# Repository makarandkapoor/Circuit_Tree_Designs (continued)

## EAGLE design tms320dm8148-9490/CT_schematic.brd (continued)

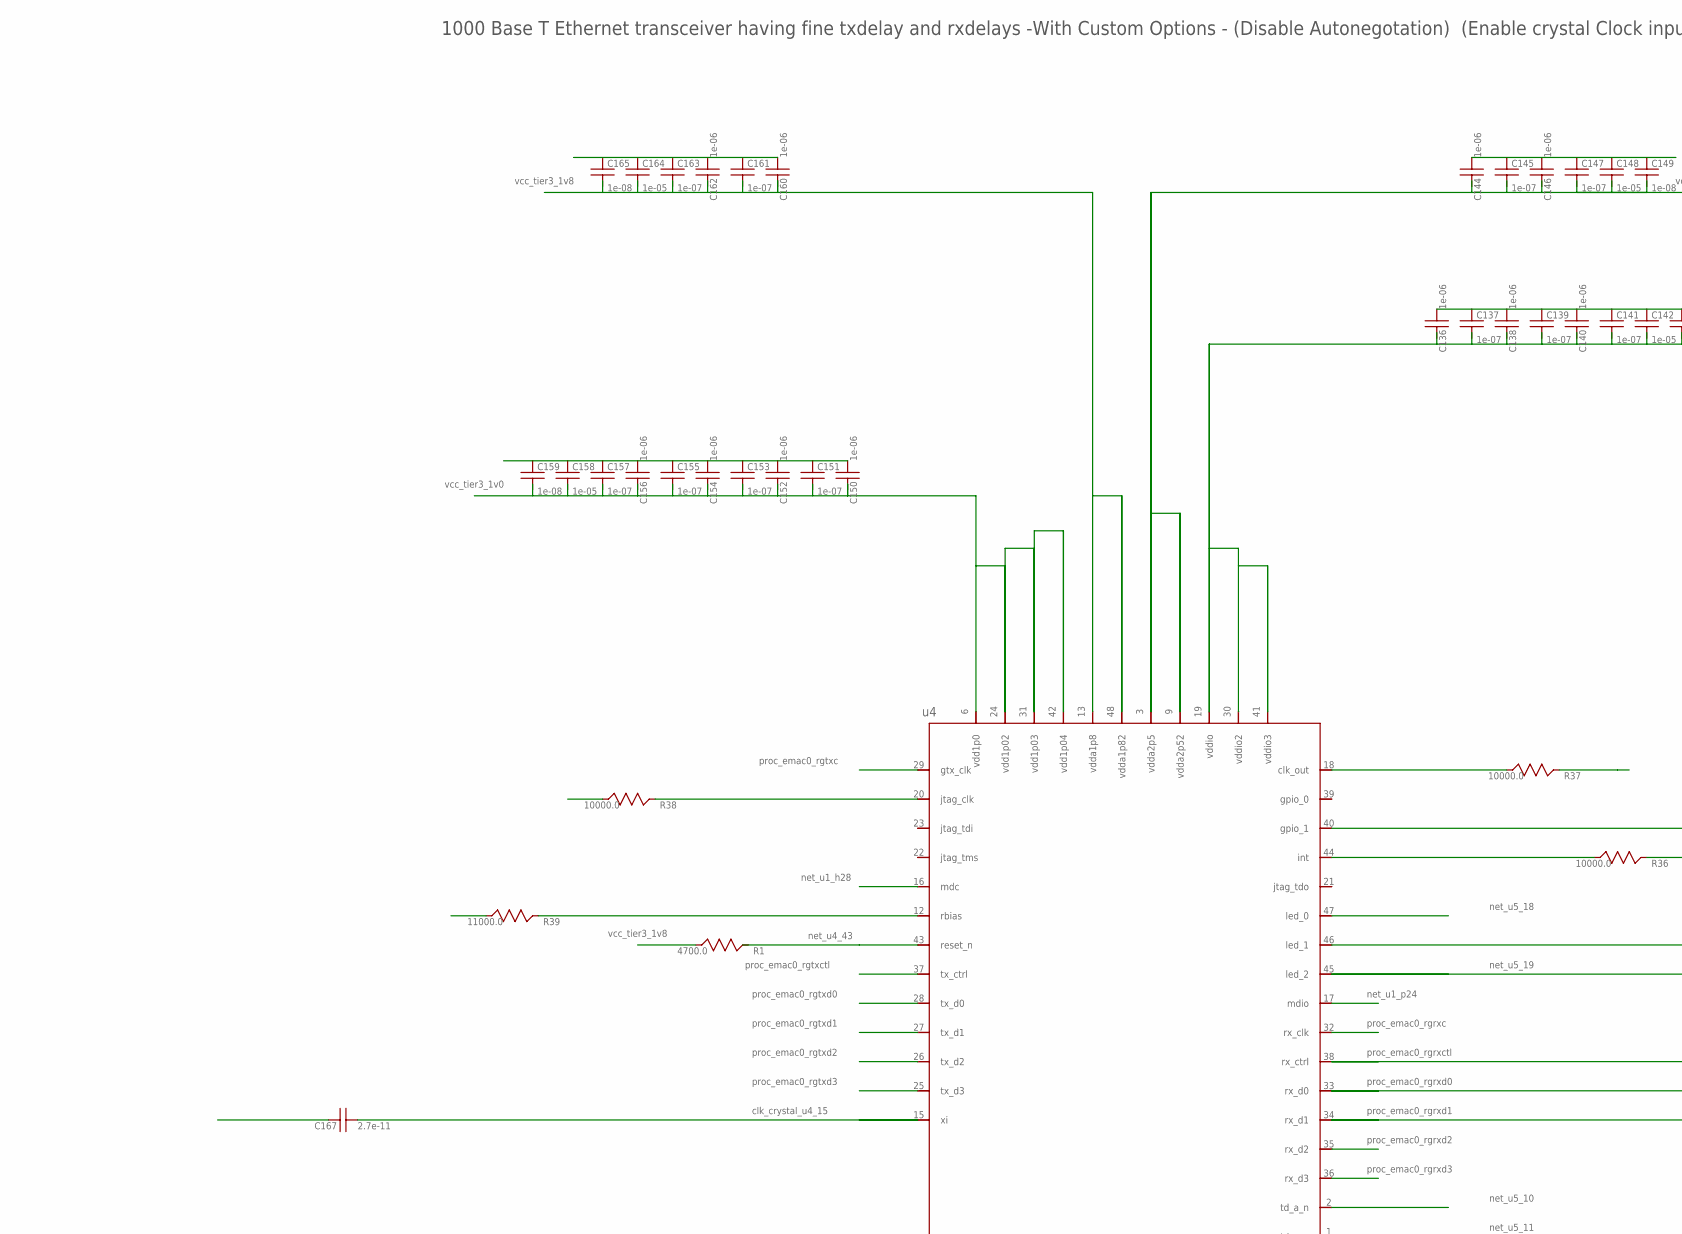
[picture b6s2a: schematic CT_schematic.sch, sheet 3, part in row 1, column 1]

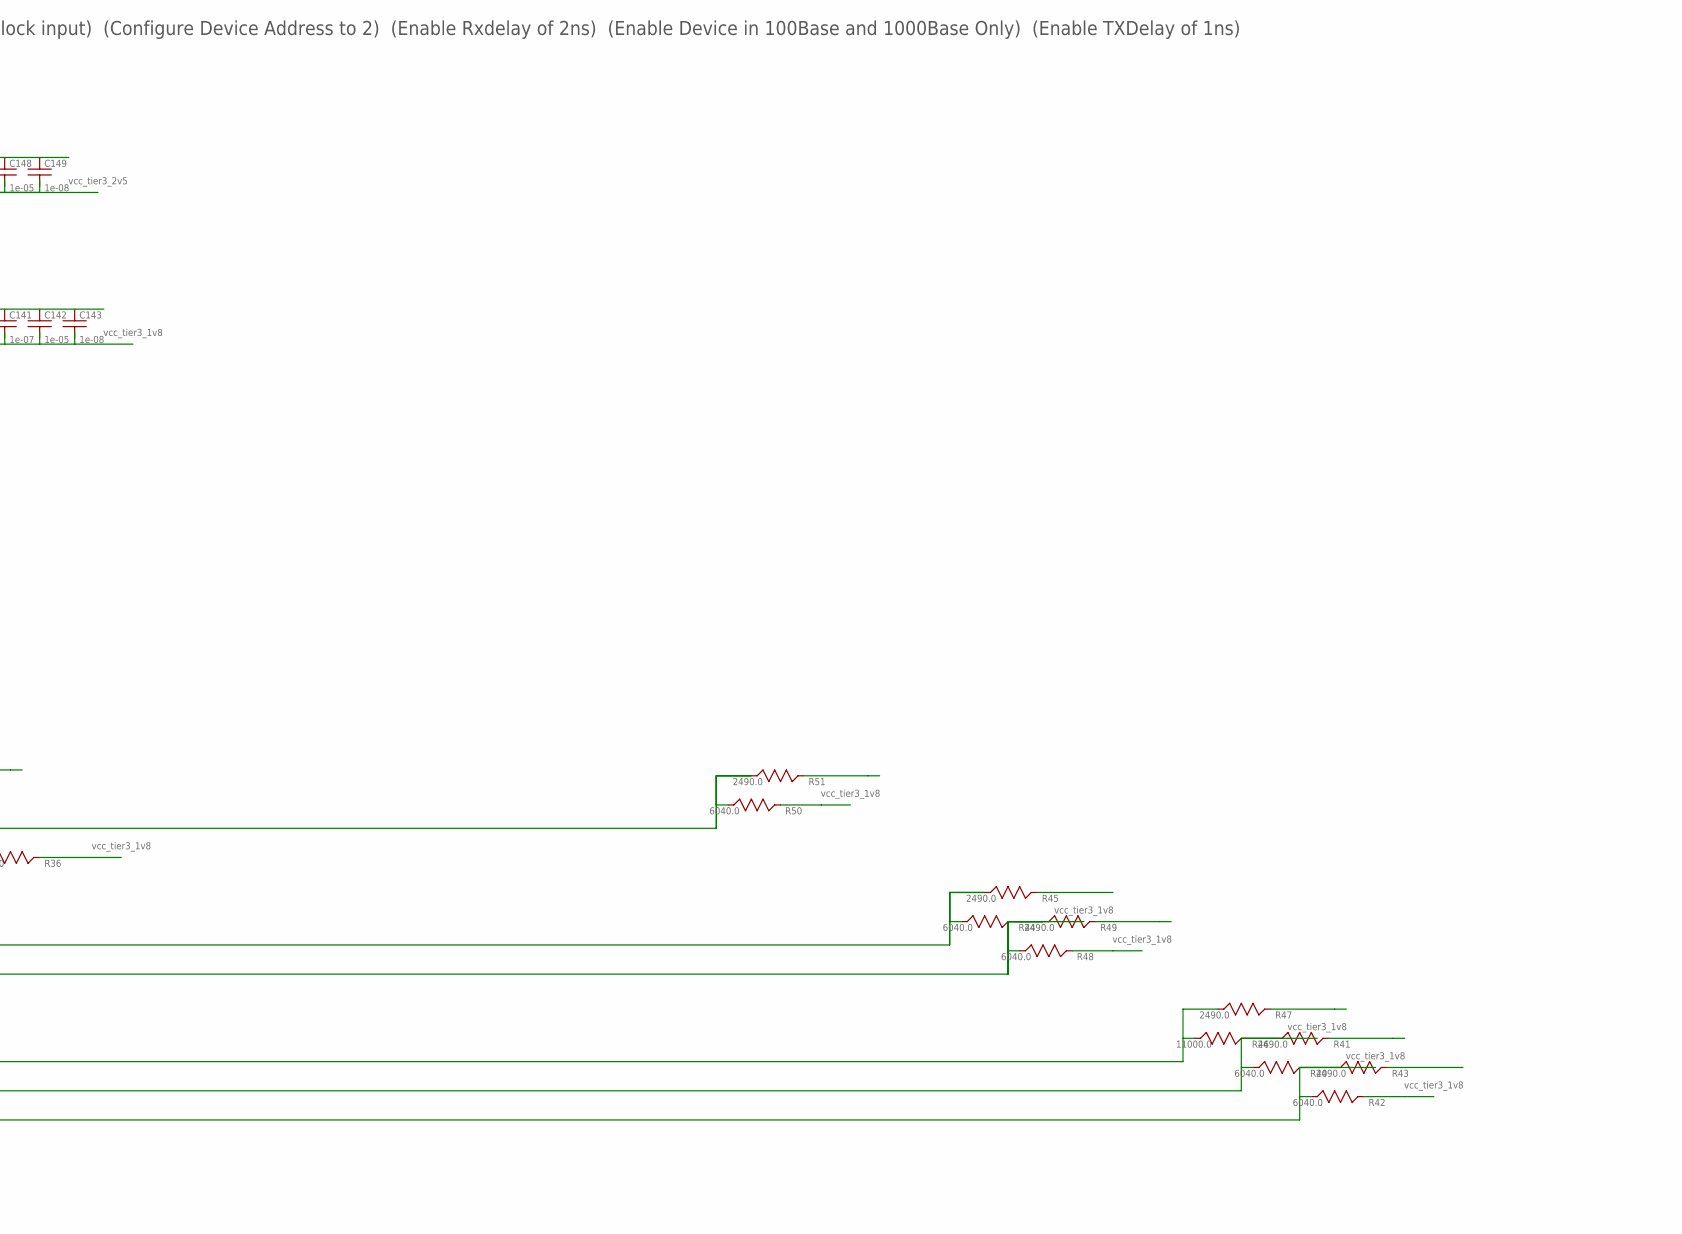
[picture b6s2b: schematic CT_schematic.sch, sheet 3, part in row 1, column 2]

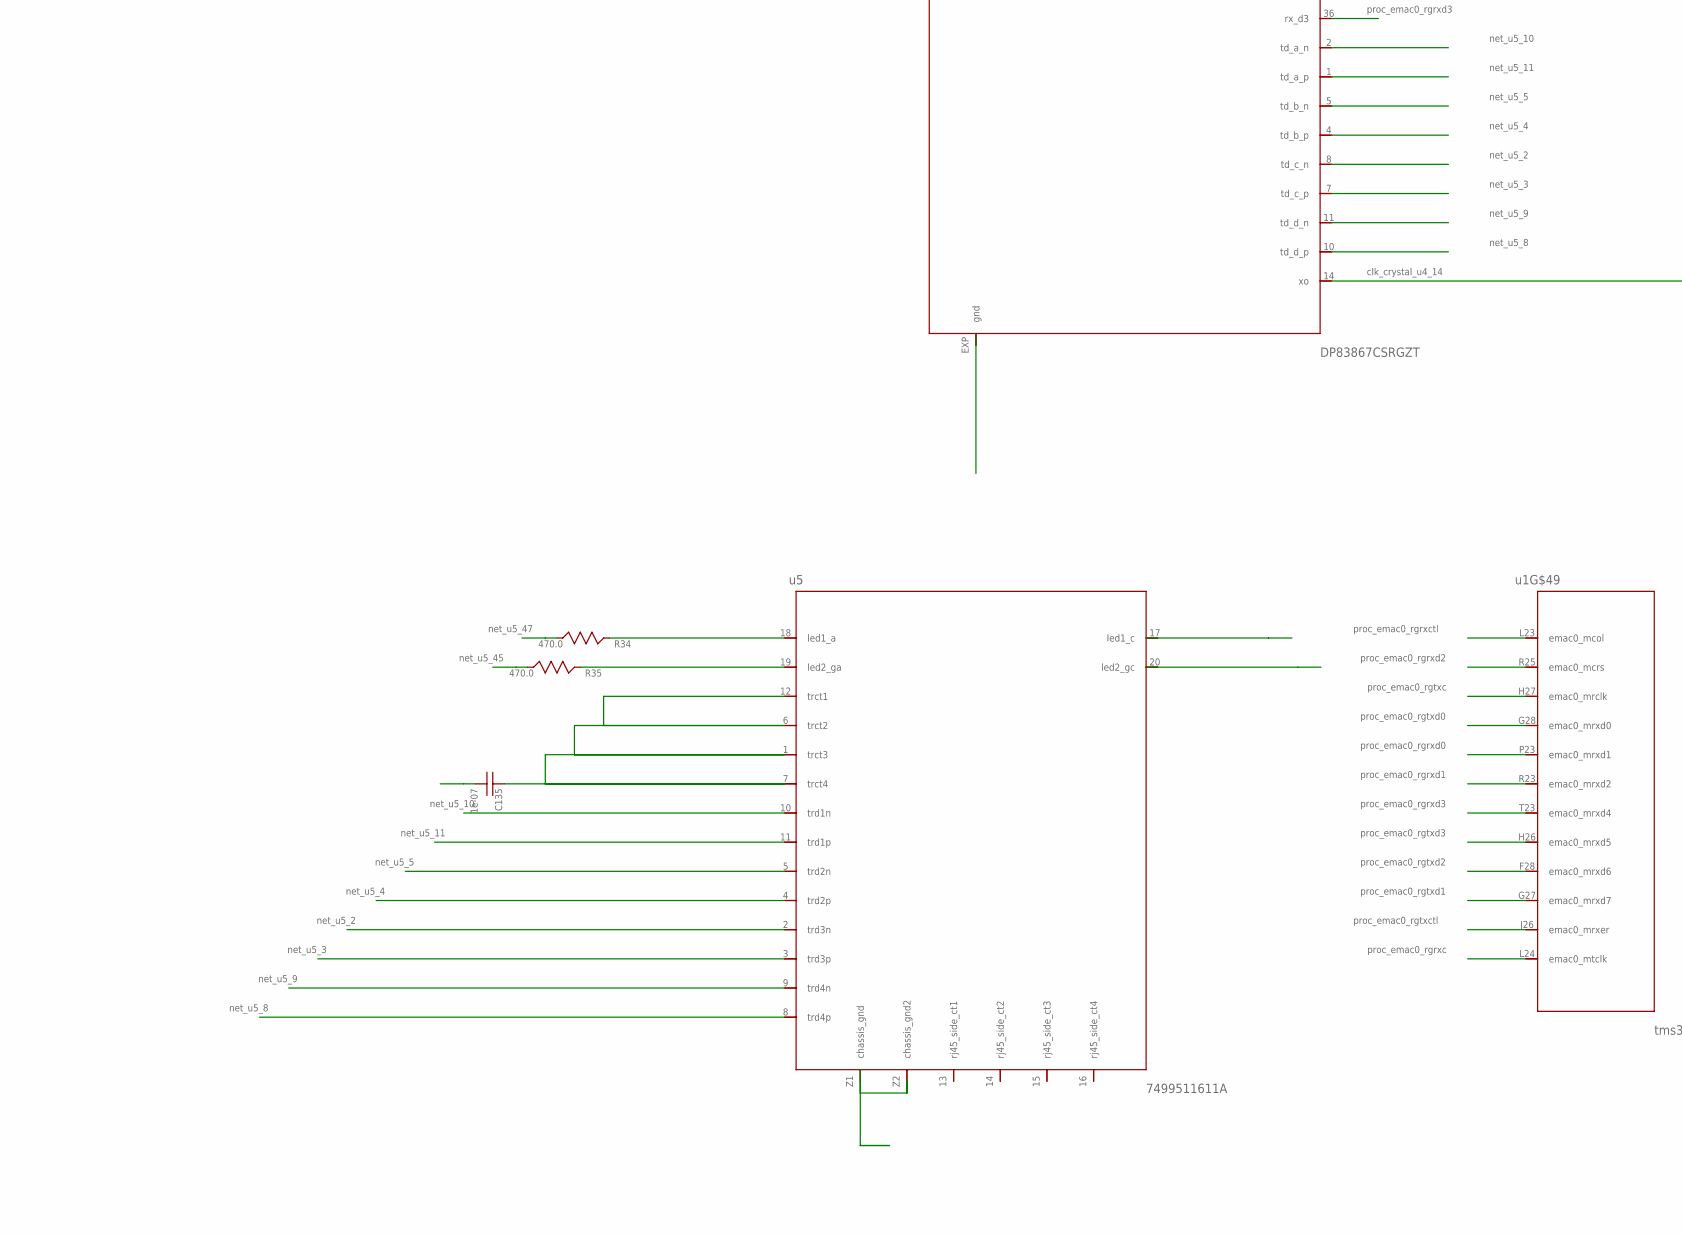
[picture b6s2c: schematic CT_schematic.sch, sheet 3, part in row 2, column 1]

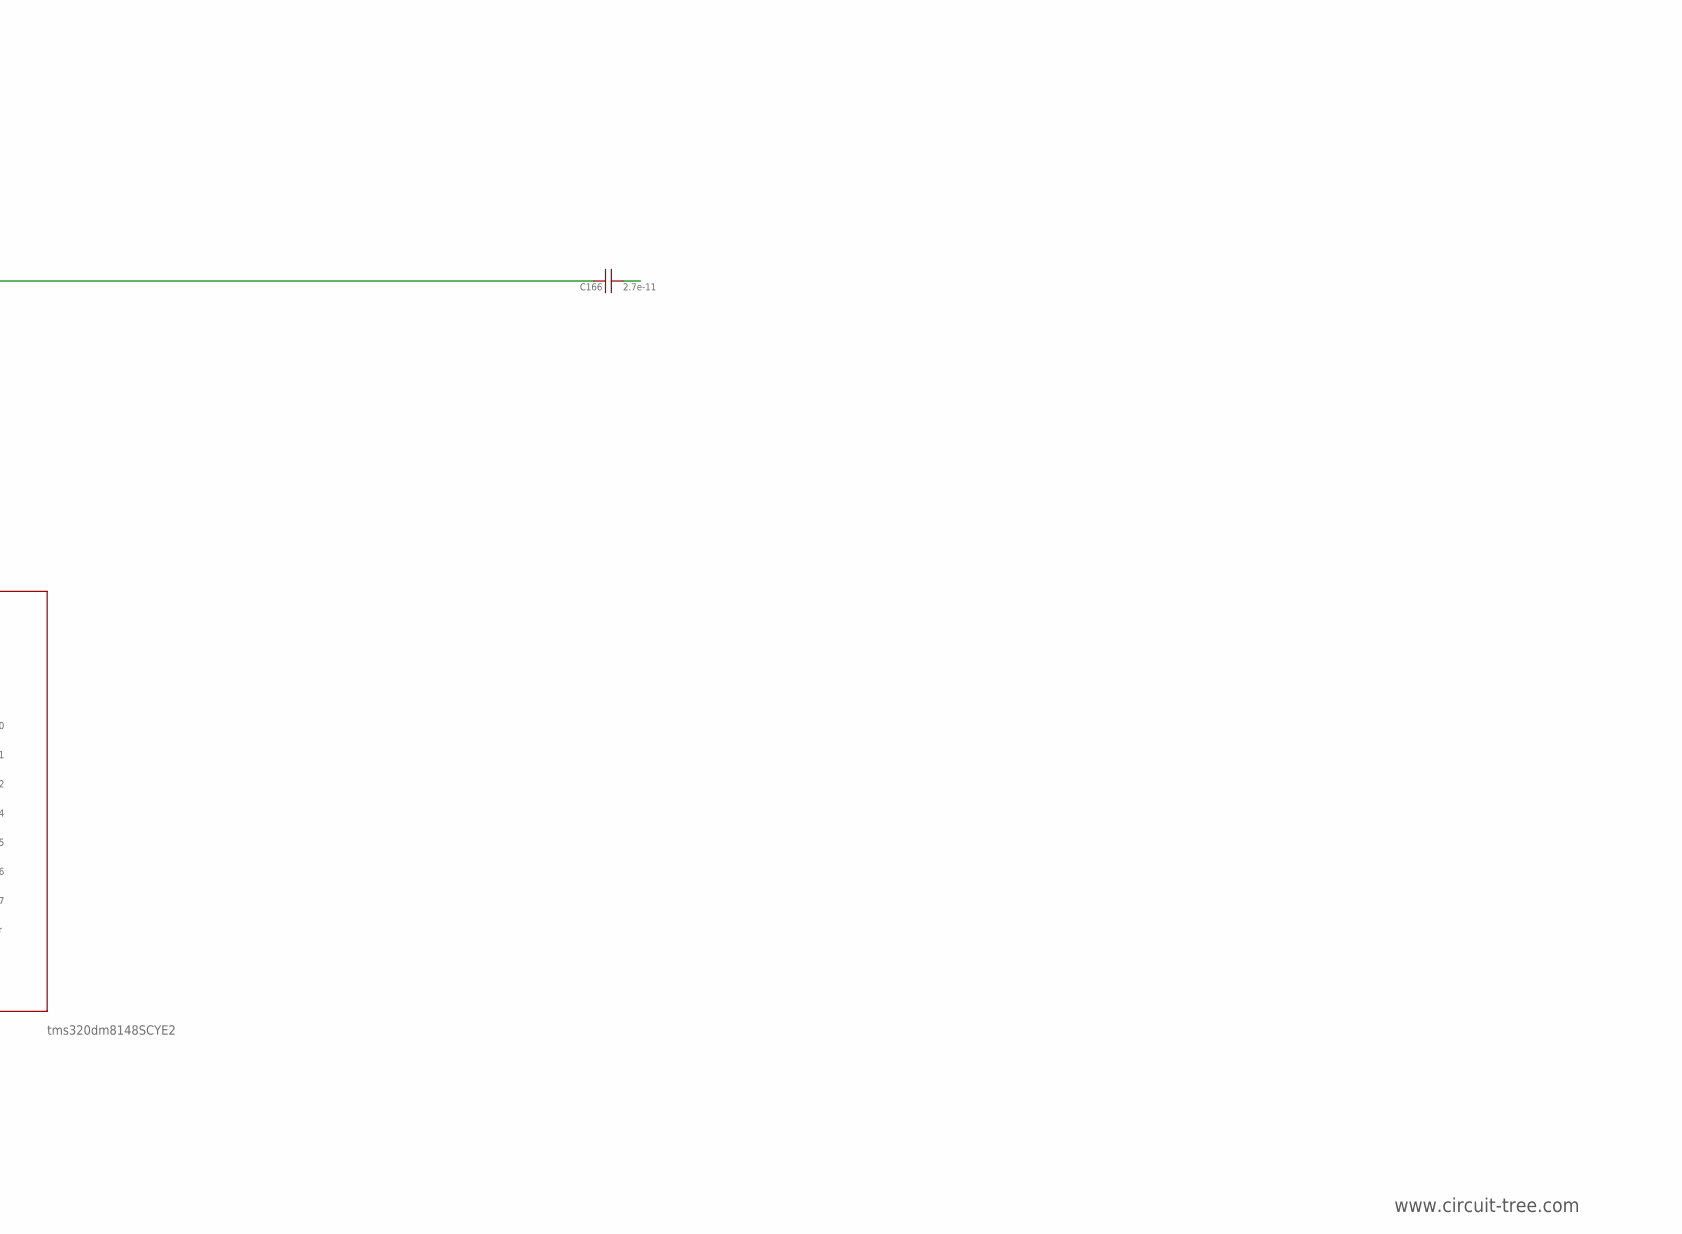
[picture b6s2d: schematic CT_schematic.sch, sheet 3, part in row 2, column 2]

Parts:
C135, C137, C139, C141, C145, C147, C151, C153, C155, C157, C161, C163: 1e-07; C0402
C136, C138, C140, C144, C146, C150, C152, C154, C156, C160, C162: 1e-06; C0603
C142, C148, C158, C164: 1e-05; C0805
C143, C149, C159, C165: 1e-08; C0402
C166, C167: 2.7e-11; C0402
R1: 4700.0; R0603
R34, R35: 470.0; R0603
R36, R37, R38: 10000.0; R0603
R39, R46: 11000.0; R0603
R40, R42, R44, R48, R50: 6040.0; R0603
R41, R43, R45, R47, R49, R51: 2490.0; R0603
u1: tms320dm8148SCYE2; BFBGA-684
u4: DP83867CSRGZT; VFQFPN48
u5: 7499511611A

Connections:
CLK_CRYSTAL_U4_14: C166.1, u4.14 (xo); also elsewhere on the board
CLK_CRYSTAL_U4_15: C167.1, u4.15 (xi); also elsewhere on the board
NET_U4_12: R39.1, u4.12 (rbias); also elsewhere on the board
NET_U4_18: R37.1, u4.18 (clk_out); also elsewhere on the board
NET_U4_20: R38.1, u4.20 (jtag_clk); also elsewhere on the board
NET_U4_40: R50.1, R51.1, u4.40 (gpio_1); also elsewhere on the board
NET_U4_43: R1.1, u4.43 (reset_n); also elsewhere on the board
NET_U4_44: R36.1, u4.44 (int); also elsewhere on the board
NET_U4_45: R35.2, R48.1, R49.1, u4.45 (led_2); also elsewhere on the board
NET_U4_46: R44.1, R45.1, u4.46 (led_1); also elsewhere on the board
NET_U5_6: C135.1, u5.1 (trct3), u5.6 (trct2), u5.7 (trct4), u5.12 (trct1); also elsewhere on the board
NET_U5_18: R34.1, u5.18 (led1_a); also elsewhere on the board
NET_U5_19: R35.1, u5.19 (led2_ga); also elsewhere on the board
NET_U5_45: R35.2
NET_U5_47: R34.2
unnamed: u1.F28 (emac0_mrxd6), u4.26 (tx_d2)
unnamed: u1.G27 (emac0_mrxd7), u4.27 (tx_d1)
unnamed: u1.G28 (emac0_mrxd0), u4.28 (tx_d0)
unnamed: u1.H26 (emac0_mrxd5), u4.25 (tx_d3)
unnamed: u1.H27 (emac0_mrclk), u4.29 (gtx_clk)
unnamed: u1.J26 (emac0_mrxer), u4.37 (tx_ctrl)
unnamed: u1.L24 (emac0_mtclk), u4.32 (rx_clk)
unnamed: u1.R25 (emac0_mcrs), u4.35 (rx_d2)
unnamed: u1.T23 (emac0_mrxd4), u4.36 (rx_d3)
unnamed: u4.1 (td_a_p), u5.11 (trd1p)
unnamed: u4.2 (td_a_n), u5.10 (trd1n)
unnamed: u4.4 (td_b_p), u5.4 (trd2p)
unnamed: u4.5 (td_b_n), u5.5 (trd2n)
unnamed: u4.7 (td_c_p), u5.3 (trd3p)
unnamed: u4.8 (td_c_n), u5.2 (trd3n)
unnamed: u4.10 (td_d_p), u5.8 (trd4p)
unnamed: u4.11 (td_d_n), u5.9 (trd4n)
PROC_EMAC0_RGRXCTL: R46.1, R47.1, u1.L23 (emac0_mcol), u4.38 (rx_ctrl); also elsewhere on the board
PROC_EMAC0_RGRXD0: R40.1, R41.1, u1.P23 (emac0_mrxd1), u4.33 (rx_d0); also elsewhere on the board
PROC_EMAC0_RGRXD1: R42.1, R43.1, u1.R23 (emac0_mrxd2), u4.34 (rx_d1); also elsewhere on the board
VCC_TIER3_2V5: C144.1, C145.1, C146.1, C147.1, C148.1, C149.1, u4.3 (vdda2p5), u4.9 (vdda2p52); also elsewhere on the board

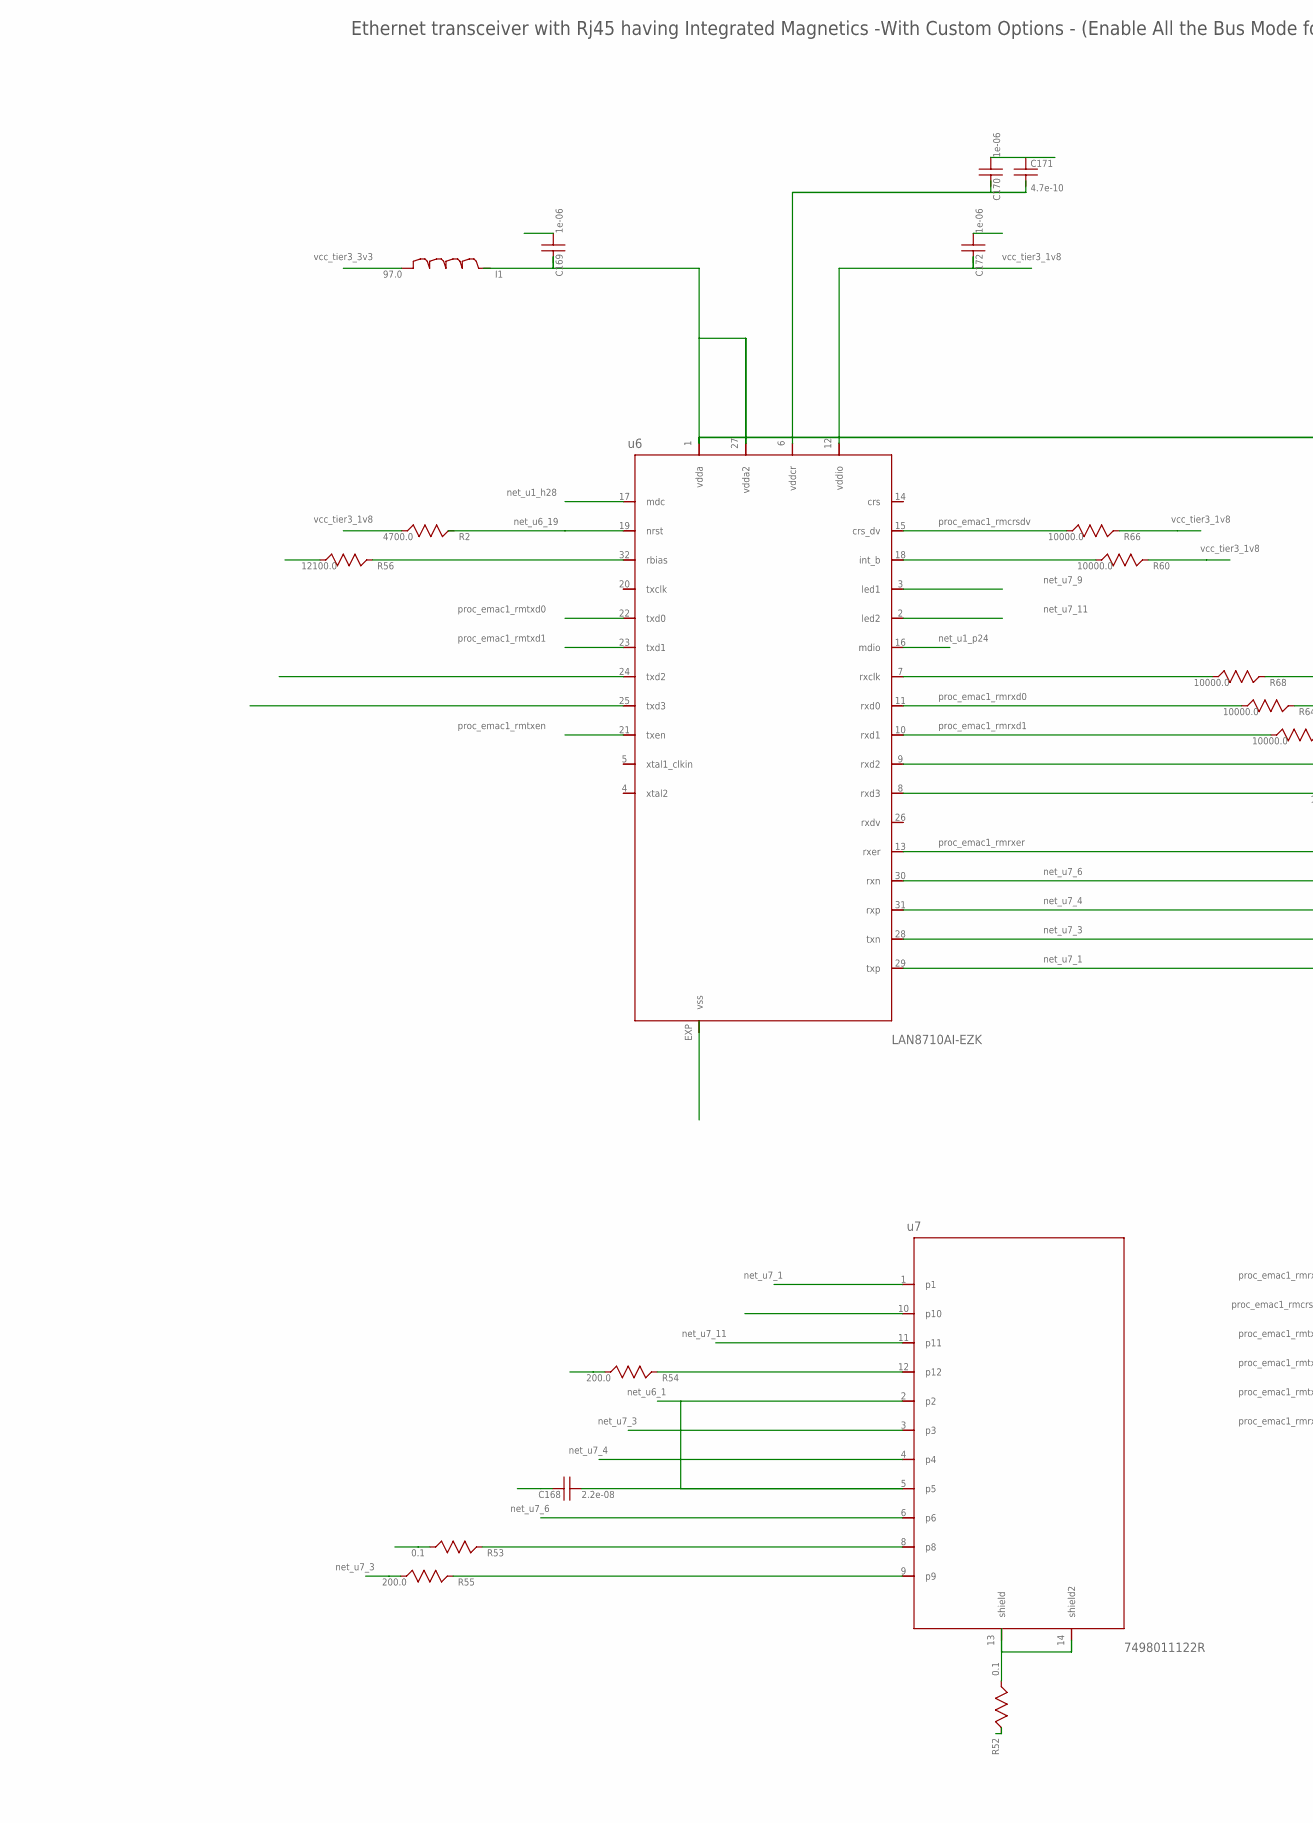
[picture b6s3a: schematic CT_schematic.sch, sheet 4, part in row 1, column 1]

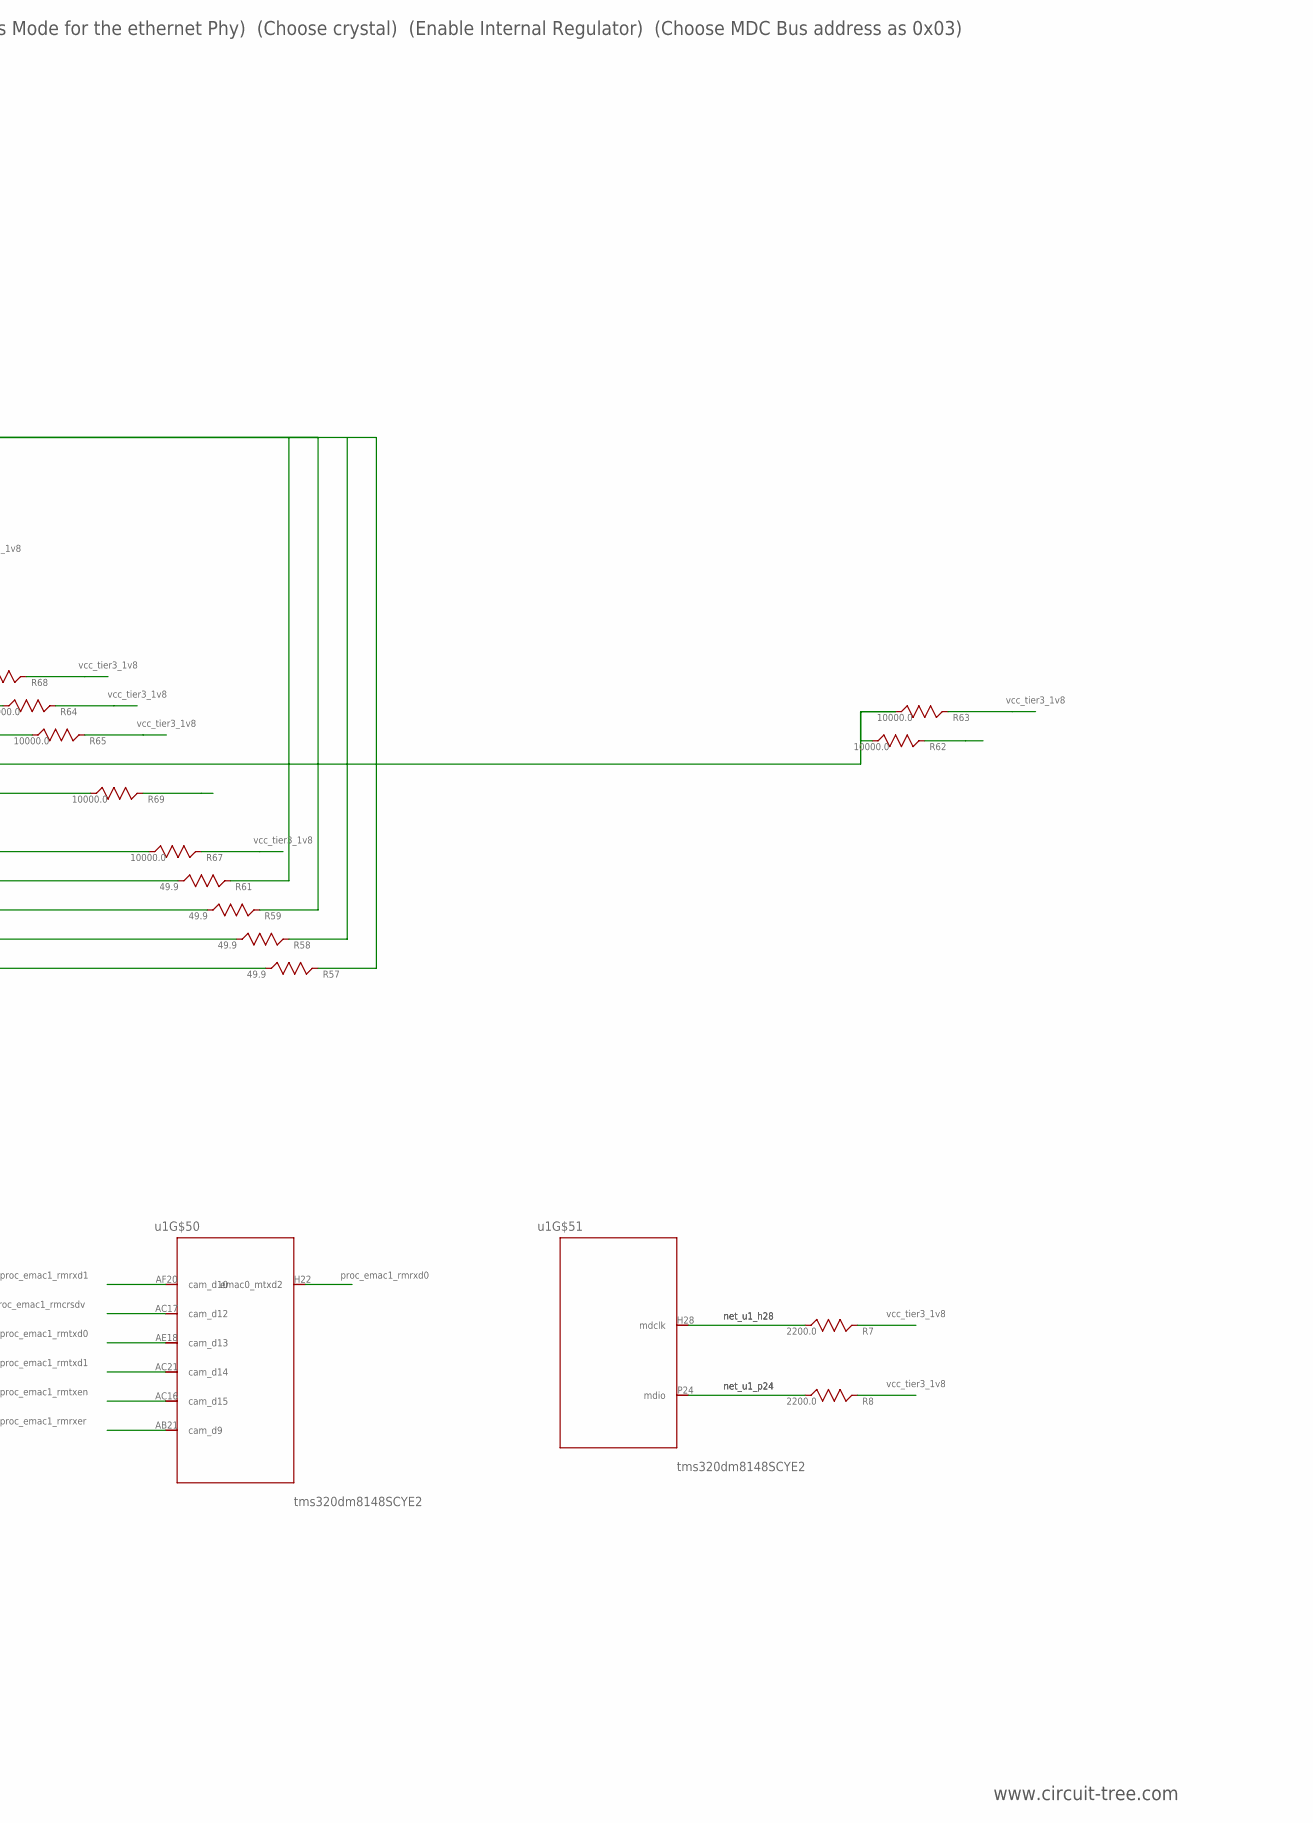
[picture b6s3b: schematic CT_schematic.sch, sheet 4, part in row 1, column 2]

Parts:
C168: 2.2e-08; C0402
C169, C170, C172: 1e-06; C0603
C171: 4.7e-10; C0603
I1: 97.0; R0603
R2: 4700.0; R0603
R7, R8: 2200.0; R0603
R52, R53: 0.1; R0603
R54, R55: 200.0; R0603
R56: 12100.0; R0603
R57, R58, R59, R61: 49.9; R0603
R60, R62, R63, R64, R65, R66, R67, R68, R69: 10000.0; R0603
u1: tms320dm8148SCYE2; BFBGA-684
u6: LAN8710AI-EZK; QFN-32
u7: 7498011122R

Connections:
NET_U1_H28: R7.1, u1.H28 (mdclk), u6.17 (mdc); also elsewhere on the board
NET_U1_P24: R8.1, u1.P24 (mdio), u6.16 (mdio); also elsewhere on the board
NET_U6_1: C169.1, I1.1, R57.2, R58.2, R59.2, R61.2, u6.1 (vdda), u6.27 (vdda2); also elsewhere on the board
NET_U6_6: C170.1, C171.1, u6.6 (vddcr); also elsewhere on the board
NET_U6_7: R68.1, u6.7 (rxclk); also elsewhere on the board
NET_U6_8: R69.1, u6.8 (rxd3); also elsewhere on the board
NET_U6_9: R62.1, R63.1, u6.9 (rxd2); also elsewhere on the board
NET_U6_18: R60.1, u6.18 (int_b); also elsewhere on the board
NET_U6_19: R2.1, u6.19 (nrst); also elsewhere on the board
NET_U6_32: R56.1, u6.32 (rbias); also elsewhere on the board
NET_U7_1: R57.1; also elsewhere on the board
NET_U7_3: R55.2, R58.1, u6.28 (txn), u7.3 (p3); also elsewhere on the board
NET_U7_4: R59.1; also elsewhere on the board
NET_U7_5: C168.1, u7.2 (p2), u7.5 (p5); also elsewhere on the board
NET_U7_6: R61.1; also elsewhere on the board
NET_U7_8: R53.1, u7.8 (p8); also elsewhere on the board
NET_U7_9: R55.1, u7.9 (p9); also elsewhere on the board
NET_U7_12: R54.1, u7.12 (p12); also elsewhere on the board
NET_U7_13: R52.1; also elsewhere on the board
unnamed: u1.AC16 (cam_d15), u6.21 (txen)
unnamed: u1.AC21 (cam_d14), u6.23 (txd1)
unnamed: u1.AE18 (cam_d13), u6.22 (txd0)
unnamed: u6.2 (led2), u7.11 (p11)
unnamed: u6.29 (txp), u7.1 (p1)
unnamed: u6.30 (rxn), u7.6 (p6)
unnamed: u6.31 (rxp), u7.4 (p4)
unnamed: u7.13 (shield), u7.14 (shield2)
PROC_EMAC1_RMCRSDV: R66.1, u1.AC17 (cam_d12), u6.15 (crs_dv); also elsewhere on the board
PROC_EMAC1_RMRXD0: R64.1, u1.H22 (emac0_mtxd2), u6.11 (rxd0); also elsewhere on the board
PROC_EMAC1_RMRXD1: R65.1, u1.AF20 (cam_d10), u6.10 (rxd1); also elsewhere on the board
PROC_EMAC1_RMRXER: R67.1, u1.AB21 (cam_d9), u6.13 (rxer); also elsewhere on the board
VCC_TIER3_3V3: I1.2; also elsewhere on the board

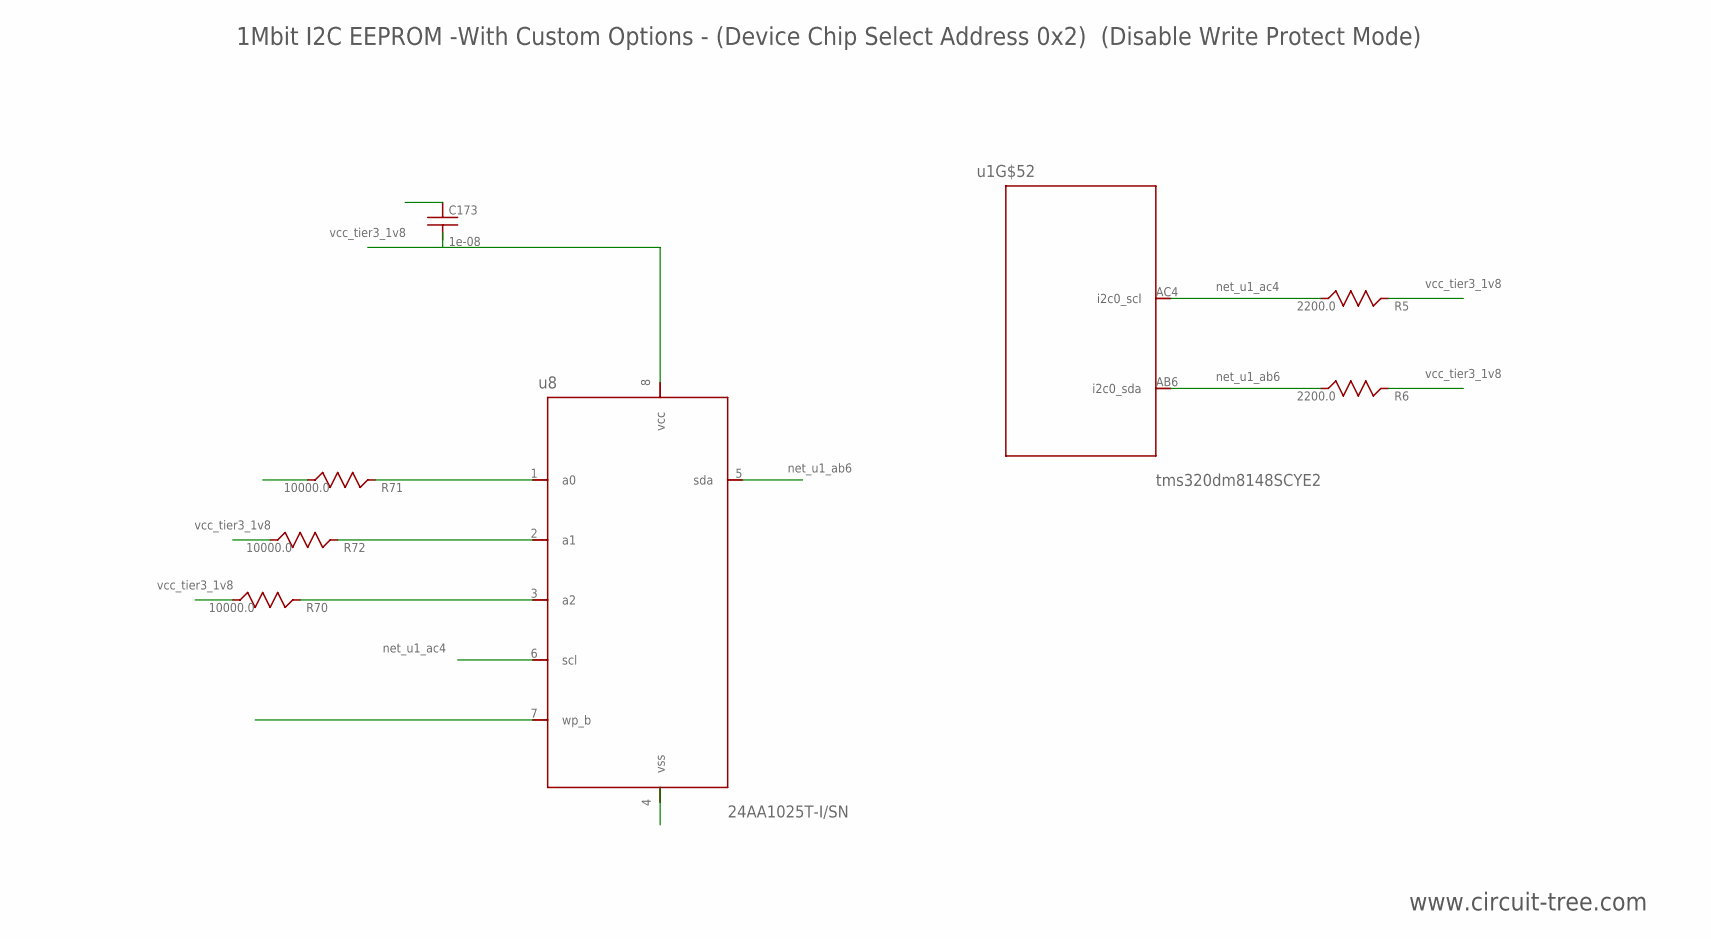
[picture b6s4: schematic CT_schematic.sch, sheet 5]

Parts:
C173: 1e-08; C0402
R5, R6: 2200.0; R0603
R70, R71, R72: 10000.0; R0603
u1: tms320dm8148SCYE2; BFBGA-684
u8: 24AA1025T-I/SN; SOIC-8

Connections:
NET_U1_AB6: R6.1, u1.AB6 (i2c0_sda), u8.5 (sda); also elsewhere on the board
NET_U1_AC4: R5.1, u1.AC4 (i2c0_scl), u8.6 (scl); also elsewhere on the board
NET_U8_1: R71.1, u8.1 (a0); also elsewhere on the board
NET_U8_2: R72.1, u8.2 (a1); also elsewhere on the board
NET_U8_3: R70.1, u8.3 (a2); also elsewhere on the board
